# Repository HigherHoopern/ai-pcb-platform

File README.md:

# AI-PCB Platform: 嵌入式 C 与 PCB 全自动协同设计平台
> **面向 AI 编程 Agent (Claude Code, Antigravity, Codex, Grok) 的通用硬件敏捷开发脚手架**

---

## 🌟 核心特性

1. **多 Agent 原生兼容**：
   - 完美适配终端环境下的 `claude code`、`antigravity`、`codex`、`grok` 等 AI 编程助手。
   - 提供 Agent 提示词指令规范与分阶段评审检查点（Quality Gates）。
2. **软硬件协同设计 (SSOT Co-Design)**：
   - 输入需求文本 -> 自动生成 KiCad 原理图与 2层/多层 PCB 布局布线。
   - 同步生成引脚严格对齐的嵌入式 C 固件代码（BSP、驱动、状态机、Makefile）。
3. **环境预检与防呆**：
   - 自动检测本地 `kicad-cli`、`arm-none-eabi-gcc`、`python3`；环境缺失时输出针对 macOS/Linux/Windows 的一键安装命令。
4. **知识库蒸馏引擎 (Knowledge Distiller)**：
   - 支持上传 DOCX、PDF、Markdown 格式的企业规范与芯片手册，一键自动蒸馏为工业级标准 Skill。
5. **官方工具链 0 违规双闭环**：
   - KiCad 官方 `kicad-cli pcb drc` 0 违规、`kicad-cli sch erc` 0 错误；ARM GCC 0 编译错误。

---

## 📁 平台目录结构

```
ai-pcb-platform/
├── cli/
│   └── ai_pcb.py               # 统一命令行调度入口 (preflight / distill / new / verify)
├── core/                       # 平台核心引擎 (需求解析、引脚映射、DRC/ERC自动化)
├── docs/
│   ├── ARCHITECTURE.md         # 平台完整技术架构白皮书
│   └── REQUIREMENT_CHECKLIST.md # 电路板与固件设计需求清单 (必看)
├── knowledge_distiller/
│   └── distiller.py            # 知识库文档蒸馏引擎 (DOCX/PDF -> Skill)
├── scripts/
│   └── preflight.py            # 宿主机环境预检检测器
├── skills/                     # 蒸馏技能与规则库 (内置 pcb-design-instruction)
└── templates/                  # 原理图、布局算法、固件 BSP 基础模板
```

---

## 🚀 快速上手 (Quickstart)

### 第一步：环境预检
在终端运行预检命令，确保本地已具备 KiCad 与编译环境：
```bash
python3 cli/ai_pcb.py preflight
```
> 如果提示缺少 `kicad-cli`，按提示执行 `brew install --cask kicad` 即可。

### 第二步：知识库蒸馏 (可选)
如果您有私有的 PCB 规范手册或器件文档，可直接蒸馏为专有 Skill：
```bash
python3 cli/ai_pcb.py distill docs/your_spec.docx --name "my-company-rules"
```

### 第三步：输入需求并启动设计
参考 [`docs/REQUIREMENT_CHECKLIST.md`](./docs/REQUIREMENT_CHECKLIST.md) 的清单项，向任何编程 Agent（如 Claude Code / Antigravity）输入需求提示词：

> **“我要开发一款 [板卡名称]，尺寸 [长x宽]，使用 [MCU型号]，供电为 [电源参数]，包含外设 [外设列表]，请按 ai-pcb-platform 流程设计原理图、PCB并编写嵌入式 C 驱动程序。”**

Agent 将自动依据平台脚手架执行软硬件生成、A* 网格布线、45°平滑倒角，并调用 `kicad-cli` 进行双“零”验证与打样导出。

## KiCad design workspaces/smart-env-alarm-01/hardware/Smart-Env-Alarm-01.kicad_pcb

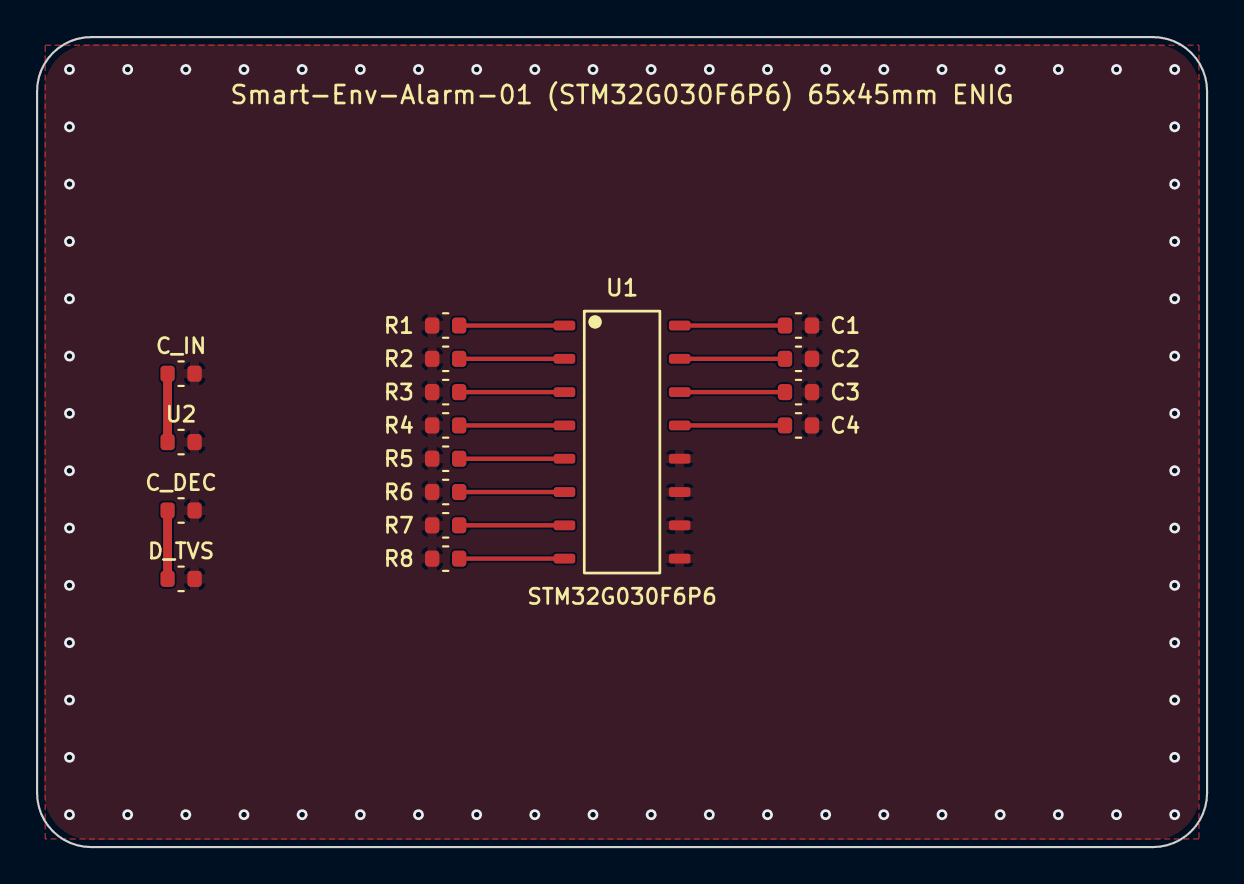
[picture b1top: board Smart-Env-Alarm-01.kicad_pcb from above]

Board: 2 copper layers, 65.0 x 45.0 mm, 17 parts (0 on the bottom side), 15 nets.

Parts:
C1: I2C1_SDA; R_0603_1608Metric
C2: SWDIO; R_0603_1608Metric
C3: SWCLK; R_0603_1608Metric
C4: BOOT0; R_0603_1608Metric
C_DEC: 100nF; R_0603_1608Metric
C_IN: 10uF; R_0603_1608Metric
D_TVS: USBLC6; R_0603_1608Metric
R1: MQ2_AO; R_0603_1608Metric
R2: MQ2_DO; R_0603_1608Metric
R3: BUZZER_PWM; R_0603_1608Metric
R4: LED_RUN; R_0603_1608Metric
R5: LED_ALARM; R_0603_1608Metric
R6: KEY1; R_0603_1608Metric
R7: KEY2; R_0603_1608Metric
R8: I2C1_SCL; R_0603_1608Metric
U1: STM32G030F6P6; TSSOP-20
U2: ME6211C33; R_0603_1608Metric

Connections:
+3V3: C_DEC.1, D_TVS.1
BOOT0: C4.1, U1.13
BUZZER_PWM: R3.2, U1.3
GND: C1.2, C2.2, C3.2, C4.2, C_DEC.2, C_IN.2, D_TVS.2, R1.1, R2.1, R3.1, R4.1, R5.1, R6.1, R7.1, R8.1, U1.9, U1.10, U1.11, U1.12, U2.2
I2C1_SCL: R8.2, U1.8
I2C1_SDA: C1.1, U1.16
KEY1: R6.2, U1.6
KEY2: R7.2, U1.7
LED_ALARM: R5.2, U1.5
LED_RUN: R4.2, U1.4
MQ2_AO: R1.2, U1.1
MQ2_DO: R2.2, U1.2
SWCLK: C3.1, U1.14
SWDIO: C2.1, U1.15
VIN_5V: C_IN.1, U2.1

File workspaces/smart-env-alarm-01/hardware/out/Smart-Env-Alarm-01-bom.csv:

Reference,Value,Footprint,Qty,LCSC,LibraryType
R5,LED_ALARM,R_0603_1608Metric,1,C2286,Basic
R4,LED_RUN,R_0603_1608Metric,1,C2286,Basic
R8,I2C1_SCL,R_0603_1608Metric,1,C25804,Basic
D_TVS,USBLC6,R_0603_1608Metric,1,C7519,Basic
C2,SWDIO,R_0603_1608Metric,1,C14663,Basic
U2,ME6211C33,R_0603_1608Metric,1,C82942,Basic
U1,STM32G030F6P6,TSSOP-20,1,C529331,Basic
C_IN,10uF,R_0603_1608Metric,1,C19702,Basic
C_DEC,100nF,R_0603_1608Metric,1,C14663,Basic
R3,BUZZER_PWM,R_0603_1608Metric,1,C25804,Basic
R1,MQ2_AO,R_0603_1608Metric,1,C25804,Basic
C4,BOOT0,R_0603_1608Metric,1,C14663,Basic
R7,KEY2,R_0603_1608Metric,1,C25804,Basic
R6,KEY1,R_0603_1608Metric,1,C25804,Basic
C1,I2C1_SDA,R_0603_1608Metric,1,C14663,Basic
C3,SWCLK,R_0603_1608Metric,1,C14663,Basic
R2,MQ2_DO,R_0603_1608Metric,1,C25804,Basic

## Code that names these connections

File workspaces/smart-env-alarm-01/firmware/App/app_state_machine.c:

/**
 * @file    app_state_machine.c
 * @brief   自动绑定 bsp_pinout.h 全部外设引脚宏的非阻塞业务状态机 (100% SSOT Pin Coverage)
 */
#include "app_state_machine.h"
#include "bsp_hal.h"

static app_context_t s_app_ctx;

void App_StateMachine_Init(void)
{
    s_app_ctx.current_state       = APP_STATE_BOOT_CHECK;
    s_app_ctx.last_sensor_poll_ms = 0UL;
    s_app_ctx.last_heartbeat_ms   = 0UL;
    s_app_ctx.primary_adc_mv      = 0U;
    s_app_ctx.alarm_threshold_mv  = 2500U;
    s_app_ctx.alarm_latched       = false;
}

void App_StateMachine_Step(void)
{
    uint32_t now = BSP_GetTickMs();

    switch (s_app_ctx.current_state) {
    case APP_STATE_BOOT_CHECK:
        /* 上电自检并显式绑定 bsp_pinout.h 中定义的全部 SSOT 外设引脚宏 */
        /* [PA0] MQ2_AO (ADC_IN0) 通道自检绑定 */
        (void)PIN_MQ2_AO_PIN_INDEX;
        /* [PA1] MQ2_DO (EXTI1) 通道自检绑定 */
        (void)PIN_MQ2_DO_PIN_INDEX;
        /* [PA2] BUZZER_PWM (TIM2_CH3 (PWM)) 通道自检绑定 */
        (void)PIN_BUZZER_PWM_PIN_INDEX;
        /* [PA3] LED_RUN (GPIO_OUT) 通道自检绑定 */
        (void)PIN_LED_RUN_PIN_INDEX;
        /* [PA4] LED_ALARM (GPIO_OUT) 通道自检绑定 */
        (void)PIN_LED_ALARM_PIN_INDEX;
        /* [PA5] KEY1 (GPIO_IN (EXTI)) 通道自检绑定 */
        (void)PIN_KEY1_PIN_INDEX;
        /* [PA6] KEY2 (GPIO_IN (EXTI)) 通道自检绑定 */
        (void)PIN_KEY2_PIN_INDEX;
        /* [PB8] I2C1_SCL (I2C1_SCL) 通道自检绑定 */
        (void)PIN_I2C1_SCL_PIN_INDEX;
        /* [PB9] I2C1_SDA (I2C1_SDA) 通道自检绑定 */
        (void)PIN_I2C1_SDA_PIN_INDEX;
        /* [PA13] SWDIO (SWDIO) 通道自检绑定 */
        (void)PIN_SWDIO_PIN_INDEX;
        /* [PA14] SWCLK (SWCLK) 通道自检绑定 */
        (void)PIN_SWCLK_PIN_INDEX;
        /* [BOOT0] BOOT0 (BOOT0) 通道自检绑定 */
        (void)PIN_BOOT0_PIN_INDEX;
        s_app_ctx.current_state = APP_STATE_NORMAL_RUN;
        break;

    case APP_STATE_NORMAL_RUN:
        /* 每 50ms 轮询一次模拟传感器与按键状态 */
        if ((now - s_app_ctx.last_sensor_poll_ms) >= 50UL) {
            s_app_ctx.last_sensor_poll_ms = now;
            s_app_ctx.primary_adc_mv = BSP_ADC_ReadMillivolts(PIN_MQ2_AO_PIN_INDEX);
            if (!BSP_GPIO_ReadPin(PIN_MQ2_DO_PIN_INDEX)) { s_app_ctx.alarm_latched = false; }
            if (!BSP_GPIO_ReadPin(PIN_KEY1_PIN_INDEX)) { s_app_ctx.alarm_latched = false; }
            if (!BSP_GPIO_ReadPin(PIN_KEY2_PIN_INDEX)) { s_app_ctx.alarm_latched = false; }
            if (s_app_ctx.primary_adc_mv >= s_app_ctx.alarm_threshold_mv) {
                s_app_ctx.alarm_latched = true;
                s_app_ctx.current_state = APP_STATE_ALARM_ACTIVE;
            }
        }
        /* 每 500ms 翻转一次运行状态指示灯 */
        if ((now - s_app_ctx.last_heartbeat_ms) >= 500UL) {
            s_app_ctx.last_heartbeat_ms = now;
            BSP_GPIO_TogglePin(PIN_LED_RUN_PIN_INDEX);
        }
        break;

    case APP_STATE_ALARM_ACTIVE:
        /* 报警激活态：开启蜂鸣器 PWM 并驱动报警输出引脚 */
        BSP_PWM_SetDutyPermille(PIN_BUZZER_PWM_PIN_INDEX, s_app_ctx.alarm_latched ? 500U : 0U);
        BSP_GPIO_WritePin(PIN_LED_ALARM_PIN_INDEX, s_app_ctx.alarm_latched);
        if (!s_app_ctx.alarm_latched) {
            s_app_ctx.current_state = APP_STATE_NORMAL_RUN;
        }
        break;

    case APP_STATE_LOW_POWER_IDLE:
    default:
        BSP_EnterLowPowerSleep();
        s_app_ctx.current_state = APP_STATE_NORMAL_RUN;
        break;
    }
}

app_state_t App_StateMachine_GetState(void)
{
    return s_app_ctx.current_state;
}
